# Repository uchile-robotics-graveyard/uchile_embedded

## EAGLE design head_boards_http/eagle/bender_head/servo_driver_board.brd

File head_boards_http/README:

Descripción de la carpeta:
============================

datasheets/: datasheets útiles para el proyecto. Notar que no están realmente en ésta
             carpeta, sino que sólo se hace referencia a ellos. Realmente están en el
             Dropbox de Bender. (carpeta "./New Face")

design/  : datos sobre el diseño de las placas

eagle/   : contiene proyecto para eagle con las placas del nuevas de la cabeza 
           (excepto la de los leds --> CONSEGUIRLA Y AGREGARLA AL GIT!!)

MPLABXProjects/: contiene proyecto mplab con el código para la placa principal y
           y la placa de los servos.

           Además, contiene código de ejemplo para la comunicación i2c y el uso de pwm

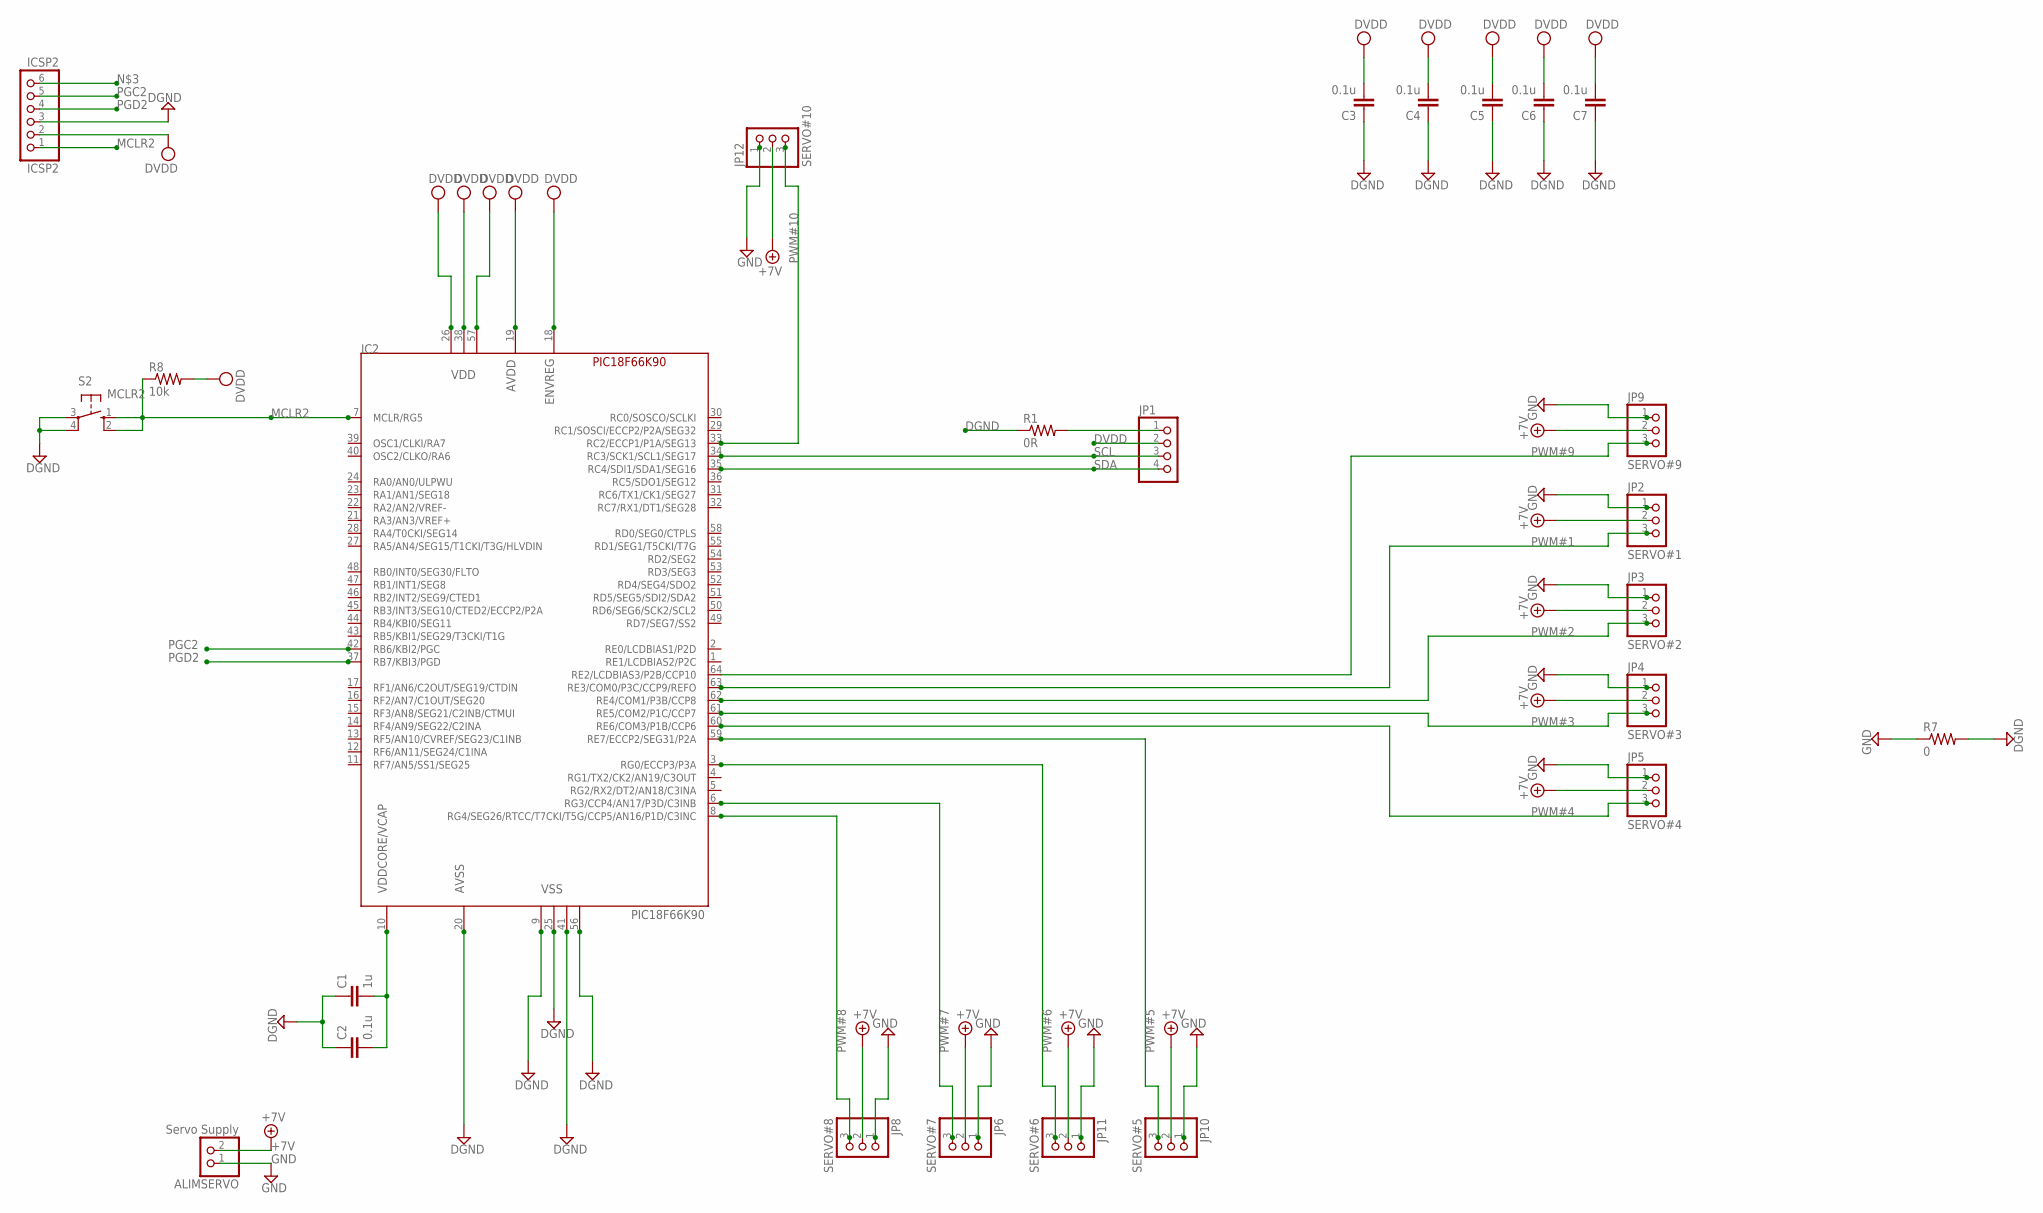
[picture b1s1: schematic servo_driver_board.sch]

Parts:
ALIMSERVO: Servo Supply; 1X02
C1: 1u; C0805
C2, C3, C4, C5, C6, C7: 0.1u; C0805
IC2: PIC18F66K90; TQFP64-10X10
ICSP2: ICSP2; 1X06
JP1: PINHD-1X4/90; 1X04/90
JP2: SERVO#1; 1X03
JP3: SERVO#2; 1X03
JP4: SERVO#3; 1X03
JP5: SERVO#4; 1X03
JP6: SERVO#7; 1X03
JP8: SERVO#8; 1X03
JP9: SERVO#9; 1X03
JP10: SERVO#5; 1X03
JP11: SERVO#6; 1X03
JP12: SERVO#10; 1X03
R1: 0R; R1206
R7: 0; R1206
R8: 10k; R1206
S2: MCLR2; B3F-10XX

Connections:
+7V: ALIMSERVO.2, JP2.2, JP3.2, JP4.2, JP5.2, JP6.2, JP8.2, JP9.2, JP10.2, JP11.2, JP12.2
DGND: C1.1, C2.1, C3.1, C4.1, C5.1, C6.1, C7.1, IC2.9 (VSS), IC2.20 (AVSS), IC2.25 (VSS), IC2.41 (VSS), IC2.56 (VSS), ICSP2.3, R1.1, R7.2, S2.3, S2.4 (P1)
DVDD: C3.2, C4.2, C5.2, C6.2, C7.2, IC2.18 (ENVREG), IC2.19 (AVDD), IC2.26 (VDD), IC2.38 (VDD), IC2.57 (VDD), ICSP2.2, JP1.2, R8.2
GND: ALIMSERVO.1, JP2.1, JP3.1, JP4.1, JP5.1, JP6.1, JP8.1, JP9.1, JP10.1, JP11.1, JP12.1, R7.1
MCLR2: IC2.7 (MCLR/RG5), ICSP2.1, R8.1, S2.1 (S), S2.2 (S1)
unnamed: JP1.1, R1.2
unnamed: C1.2, C2.2, IC2.10 (VDDCORE/VCAP)
PGC2: IC2.42 (RB6/KBI2/PGC), ICSP2.5
PGD2: IC2.37 (RB7/KBI3/PGD), ICSP2.4
PWM#1: IC2.63 (RE3/COM0/P3C/CCP9/REFO), JP2.3
PWM#2: IC2.62 (RE4/COM1/P3B/CCP8), JP3.3
PWM#3: IC2.61 (RE5/COM2/P1C/CCP7), JP4.3
PWM#4: IC2.60 (RE6/COM3/P1B/CCP6), JP5.3
PWM#5: IC2.59 (RE7/ECCP2/SEG31/P2A), JP10.3
PWM#6: IC2.3 (RG0/ECCP3/P3A), JP11.3
PWM#7: IC2.6 (RG3/CCP4/AN17/P3D/C3INB), JP6.3
PWM#8: IC2.8 (RG4/SEG26/RTCC/T7CKI/T5G/CCP5/AN16/P1D/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), JP8.3
PWM#9: IC2.64 (RE2/LCDBIAS3/P2B/CCP10), JP9.3
PWM#10: IC2.33 (RC2/ECCP1/P1A/SEG13), JP12.3
SCL: IC2.34 (RC3/SCK1/SCL1/SEG17), JP1.3
SDA: IC2.35 (RC4/SDI1/SDA1/SEG16), JP1.4

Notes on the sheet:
PWM#1
PWM#2
PWM#3
PWM#4
PWM#7
PWM#8
PWM#9
PWM#5
PWM#6
PWM#10

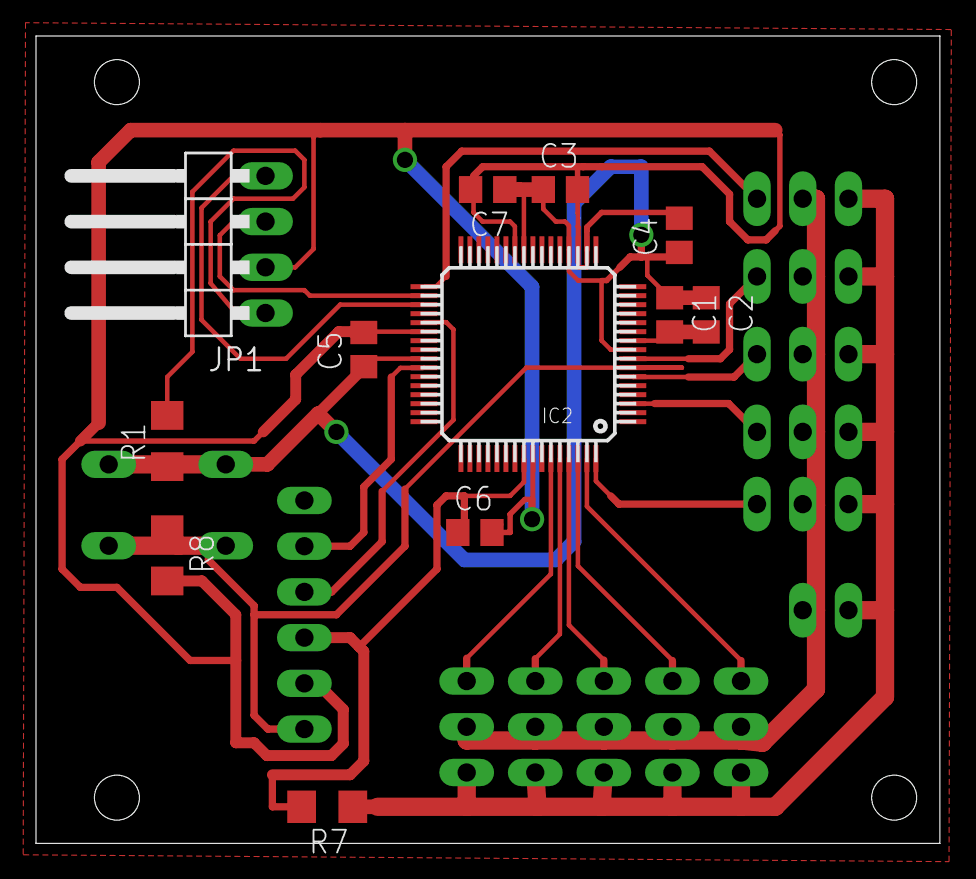
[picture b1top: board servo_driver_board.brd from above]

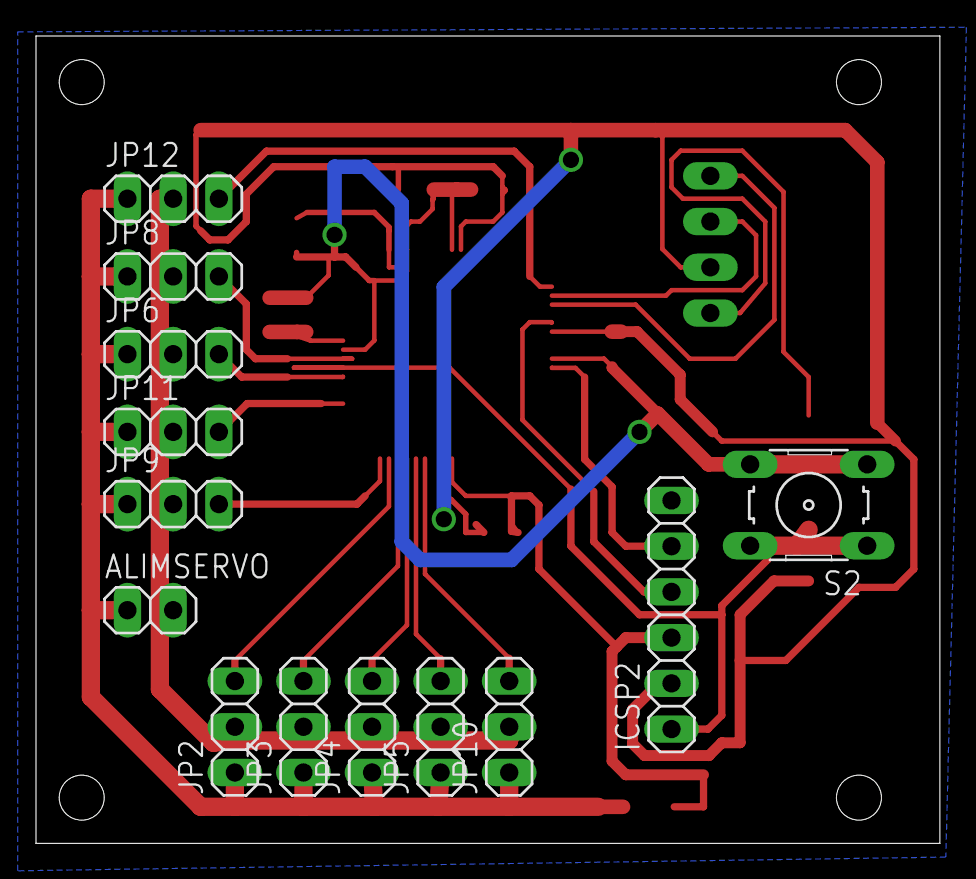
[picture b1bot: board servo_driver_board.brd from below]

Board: 2 copper layers, 50.2 x 44.9 mm, 25 parts (13 on the bottom side), 21 nets.

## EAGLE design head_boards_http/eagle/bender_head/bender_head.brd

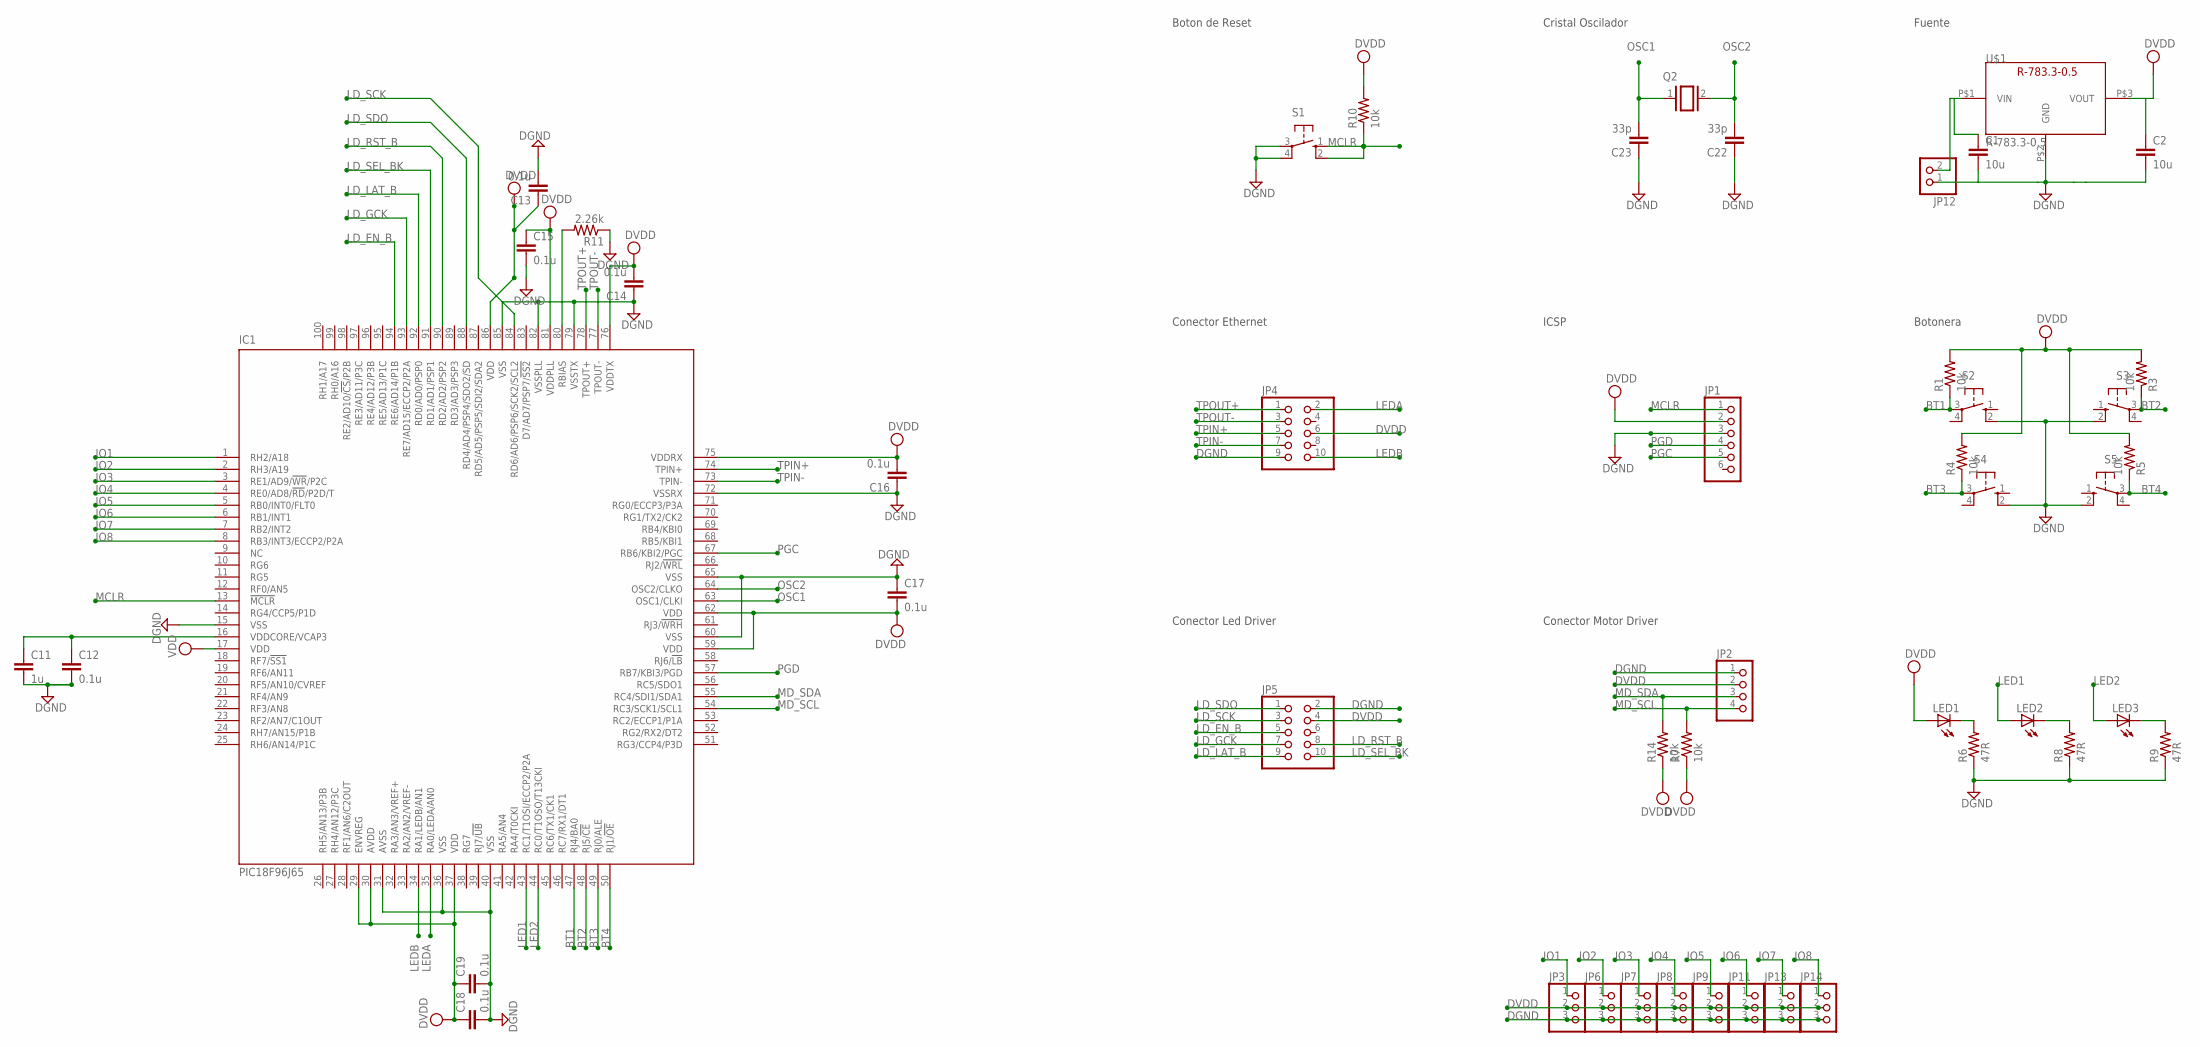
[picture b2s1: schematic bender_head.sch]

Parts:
C1, C2: 10u; C1206
C11: 1u; C1206
C12, C13, C14, C15, C16, C17, C18, C19: 0.1u; C0805
C22, C23: 33p; C1206
IC1: PIC18F96J65; TQFP100
JP1: PINHD-1X6; 1X06
JP2: PINHD-1X4/90; 1X04/90
JP3, JP6, JP7, JP8, JP9, JP11, JP13, JP14: PINHD-1X3; 1X03
JP4, JP5: PINHD-2X5/90; 2X05/90
JP12: PINHD-1X2/90; 1X02/90
LED1, LED2, LED3: LEDSML0805; SML0805
Q2: XTAL/S; QS
R1, R3, R4, R5, R7, R10, R14: 10k; R1206
R6: 47R; M0805
R8, R9: 47R; M1206
R11: 2.26k; R1206
S1, S2, S3, S4, S5: 10-XX; B3F-10XX
U$1: R-783.3-0.5

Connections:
BT1: IC1.47 (RJ4/BA0), R1.1, S2.3
BT2: IC1.48 (RJ5/!CE), R3.1, S3.3
BT3: IC1.49 (RJ0/ALE), R4.1, S4.3
BT4: IC1.50 (RJ1/!OE), R5.1, S5.3
DGND: C1.2, C2.2, C11.2, C12.2, C13.2, C14.1, C15.2, C16.1, C17.1, C18.2, C19.2, C22.1, C23.1, IC1.15 (VSS), IC1.31 (AVSS), IC1.36 (VSS), IC1.40 (VSS), IC1.60 (VSS), IC1.65 (VSS), IC1.72 (VSSRX), IC1.79 (VSSTX), IC1.82 (VSSPLL), IC1.85 (VSS), JP1.3, JP2.1, JP3.3, JP4.9, JP5.2, JP6.3, JP7.3, JP8.3, JP9.3, JP11.3, JP12.1, JP13.3, JP14.3, R6.1, R8.1, R9.1, R11.1, S1.3, S1.4 (P1), S2.2 (S1), S3.2 (S1), S4.2 (S1), S5.2 (S1), U$1.P$2 (GND)
DVDD: C2.1, C13.1, C14.2, C15.1, C16.2, C17.2, C18.1, C19.1, IC1.17 (VDD), IC1.29 (ENVREG), IC1.30 (AVDD), IC1.37 (VDD), IC1.59 (VDD), IC1.62 (VDD), IC1.75 (VDDRX), IC1.76 (VDDTX), IC1.81 (VDDPLL), IC1.86 (VDD), JP1.2, JP2.2, JP3.2, JP4.6, JP5.4, JP6.2, JP7.2, JP8.2, JP9.2, JP11.2, JP13.2, JP14.2, LED1.A, R1.2, R3.2, R4.2, R5.2, R7.1, R10.2, R14.1, U$1.P$3 (VOUT)
IO1: IC1.1 (RH2/A18), JP3.1
IO2: IC1.2 (RH3/A19), JP6.1
IO3: IC1.3 (RE1/AD9/!WR!/P2C), JP7.1
IO4: IC1.4 (RE0/AD8/!RD!/P2D/T), JP8.1
IO5: IC1.5 (RB0/INT0/FLT0), JP9.1
IO6: IC1.6 (RB1/INT1), JP11.1
IO7: IC1.7 (RB2/INT2), JP13.1
IO8: IC1.8 (RB3/INT3/ECCP2/P2A), JP14.1
LD_EN_B: IC1.94 (RE6/AD14/P1B), JP5.5
LD_GCK: IC1.93 (RE7/AD15/ECCP2/P2A), JP5.7
LD_LAT_B: IC1.92 (RD0/AD0/PSP0), JP5.9
LD_RST_B: IC1.90 (RD2/AD2/PSP2), JP5.8
LD_SCK: IC1.84 (RD6/AD6/PSP6/SCK2/SCL2), JP5.3
LD_SDO: IC1.88 (RD4/AD4/PSP4/SDO2/SD), JP5.1
LD_SEL_BK: IC1.91 (RD1/AD1/PSP1), JP5.10
LED1: IC1.43 (RC1/T1OSI/ECCP2/P2A), LED2.A
LED2: IC1.44 (RC0/T1OSO/T13CKI), LED3.A
LEDA: IC1.35 (RA0/LEDA/AN0), JP4.2
LEDB: IC1.34 (RA1/LEDB/AN1), JP4.10
MCLR: IC1.13 (!MCLR), JP1.1, R10.1, S1.1 (S), S1.2 (S1)
MD_SCL: IC1.54 (RC3/SCK1/SCL1), JP2.4, R7.2
MD_SDA: IC1.55 (RC4/SDI1/SDA1), JP2.3, R14.2
unnamed: LED1.C, R6.2
unnamed: LED2.C, R8.2
unnamed: LED3.C, R9.2
unnamed: C11.1, C12.1, IC1.16 (VDDCORE/VCAP3)
unnamed: IC1.80 (RBIAS), R11.2
OSC1: C23.2, IC1.63 (OSC1/CLKI), Q2.1
OSC2: C22.2, IC1.64 (OSC2/CLKO), Q2.2
PGC: IC1.67 (RB6/KBI2/PGC), JP1.5
PGD: IC1.57 (RB7/KBI3/PGD), JP1.4
TPIN+: IC1.74 (TPIN+), JP4.5
TPIN-: IC1.73 (TPIN-), JP4.7
TPOUT+: IC1.78 (TPOUT+), JP4.1
TPOUT-: IC1.77 (TPOUT-), JP4.3
VIN: C1.1, JP12.2, U$1.P$1 (VIN)

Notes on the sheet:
Conector Ethernet
Cristal Oscilador
Boton de Reset
Conector Led Driver
Conector Motor Driver
ICSP
Botonera
Fuente

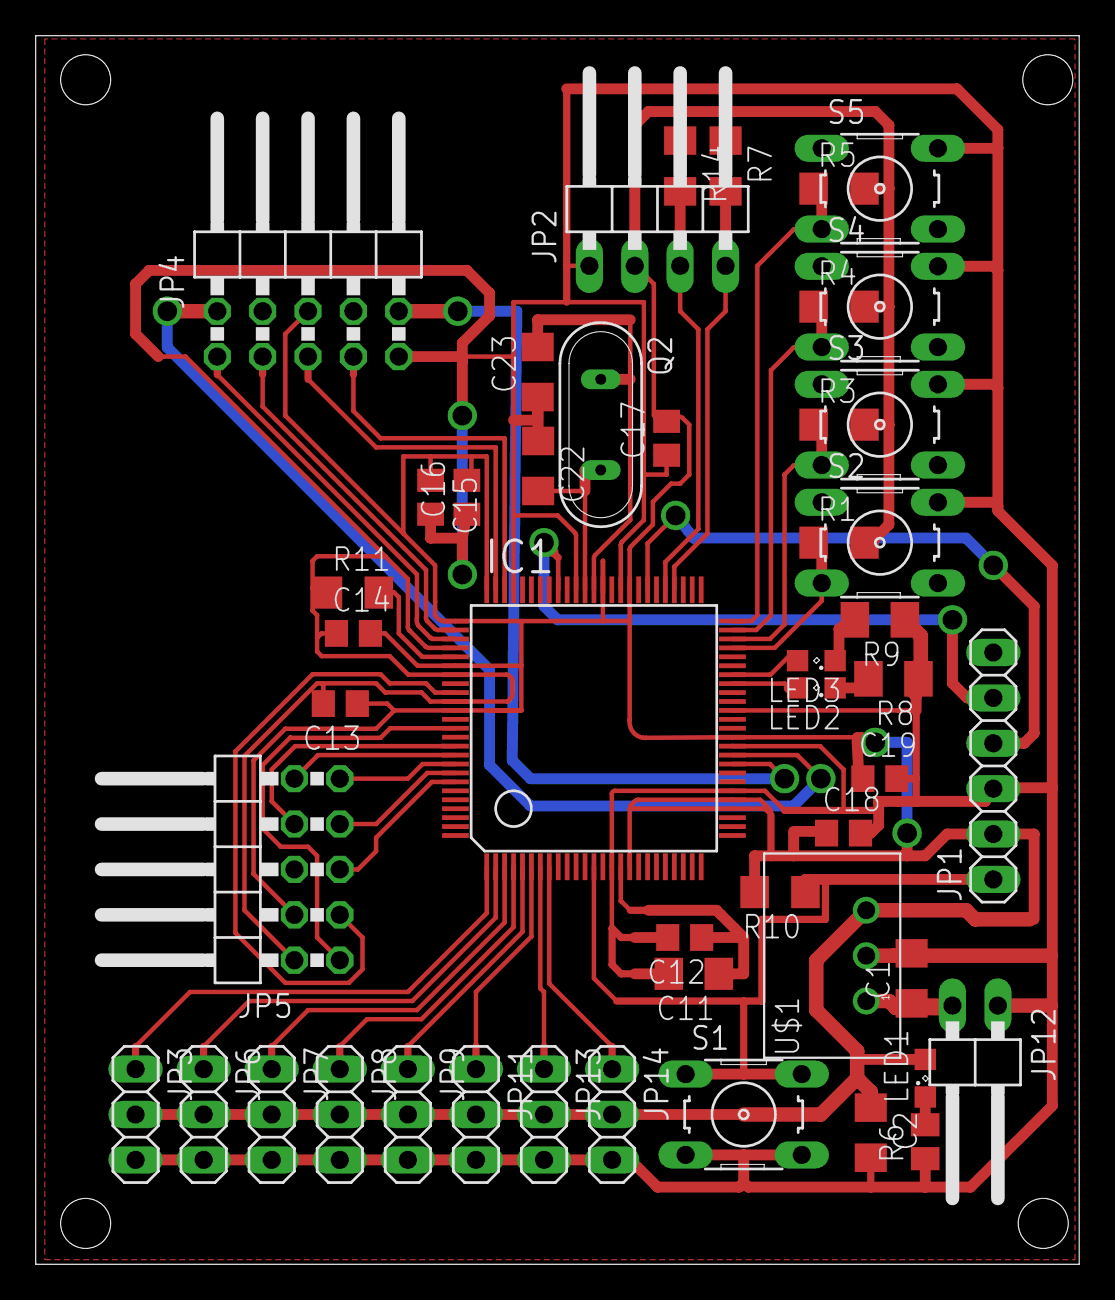
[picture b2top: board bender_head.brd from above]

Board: 2 copper layers, 58.4 x 68.8 mm, 48 parts (0 on the bottom side), 42 nets.

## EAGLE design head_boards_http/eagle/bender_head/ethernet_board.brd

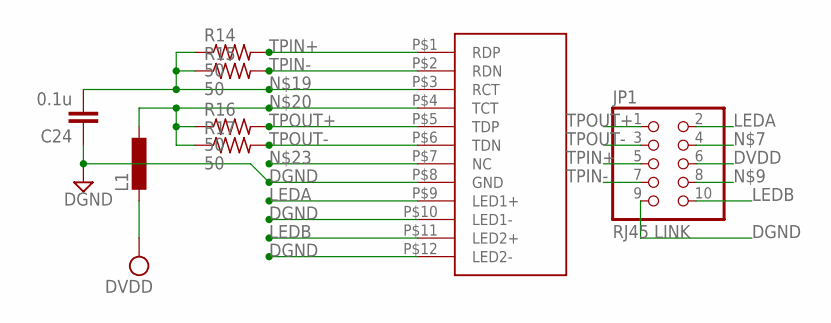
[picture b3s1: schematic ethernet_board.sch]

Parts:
C24: 0.1u; C0805
JP1: RJ45 LINK; 2X05/90
L1: L-EU0207/10; 0207/10
R14, R15, R16, R17: 50; R1206
U$5: RJ45; TYCO-RJ45

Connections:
DGND: C24.1, JP1.9, U$5.P$8 (GND), U$5.P$10 (LED1-), U$5.P$12 (LED2-)
DVDD: JP1.6, L1.2
LEDA: JP1.2, U$5.P$9 (LED1+)
LEDB: JP1.10, U$5.P$11 (LED2+)
unnamed: C24.2, R14.1, R15.1, U$5.P$3 (RCT)
unnamed: L1.1, R16.1, R17.1, U$5.P$4 (TCT)
TPIN+: JP1.5, R14.2, U$5.P$1 (RDP)
TPIN-: JP1.7, R15.2, U$5.P$2 (RDN)
TPOUT+: JP1.1, R16.2, U$5.P$5 (TDP)
TPOUT-: JP1.3, R17.2, U$5.P$6 (TDN)

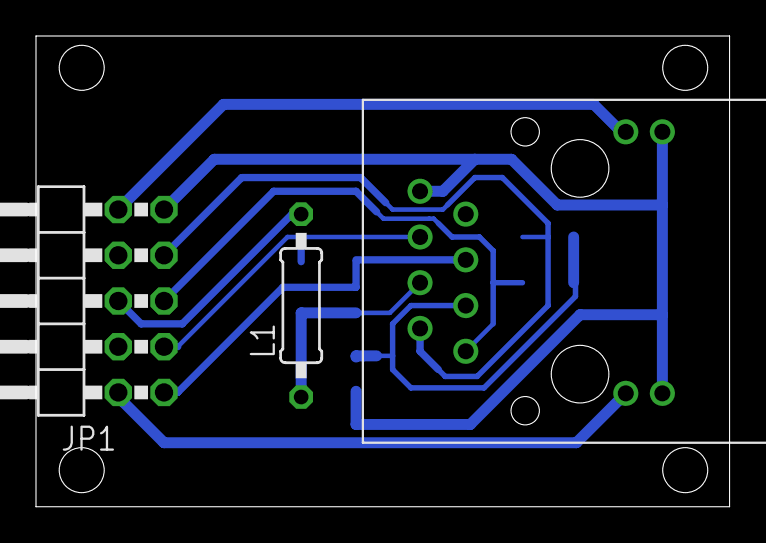
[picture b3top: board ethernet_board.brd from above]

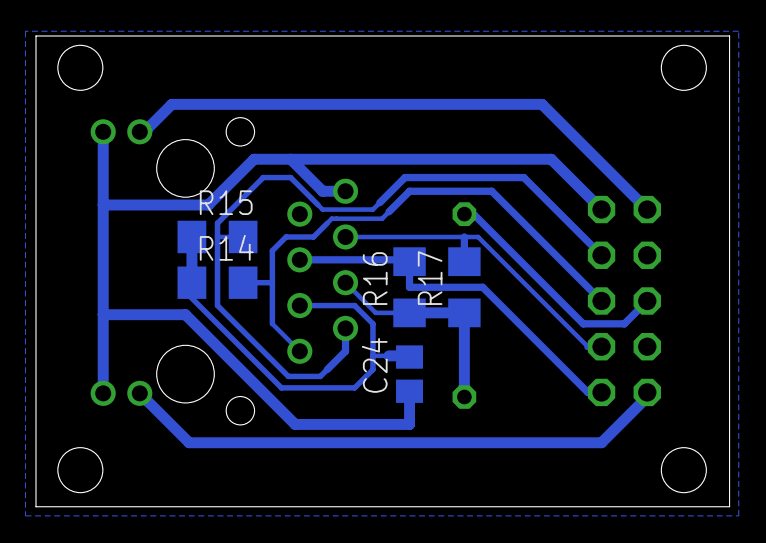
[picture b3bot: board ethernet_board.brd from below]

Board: 2 copper layers, 38.5 x 26.2 mm, 8 parts (5 on the bottom side), 10 nets.

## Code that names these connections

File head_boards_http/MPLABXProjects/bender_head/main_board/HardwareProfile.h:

 /*********************************************************************
 *
 *	Hardware specific definitions for:
 *    - PIC18F96J60
 *
 *********************************************************************
 * FileName:        HardwareProfile.h
 * Dependencies:    Compiler.h
 * Processor:       PIC18
 * Compiler:        Microchip C18 v3.36 or higher
 * Company:         Microchip Technology, Inc.
 ********************************************************************/
#ifndef HARDWARE_PROFILE_H
#define HARDWARE_PROFILE_H

#include "Compiler.h"

// Set configuration fuses (but only in MainDemo.c where THIS_IS_STACK_APPLICATION is defined)
#if defined(THIS_IS_STACK_APPLICATION)
        // WDT (ON): Watch Dog Timer
	#pragma config WDT=OFF

        /* FOSC2 ( ON ): Default/Reset System Clock Select bit. 
         * - OFF: clock=INTRC,
         * - ON : clock selected by FOSC1:FOSC0
         */
        #pragma config FOSC2=ON

        // FOSC (ECPLL): Oscillator Selection. (HS|EC) osc., (HSPLL|ECPLL) HS|EC-CLKO with PLL..
        #pragma config FOSC=HSPLL


        /* ETHLED( ON ): Ethernet LED Enable bit.
         * - ON : RA0/RA1 are multiplexed with LEDA/LEDB when Ethernet module is
         *        enabled and function as I/O when Ethernet is disabled.
         * - OFF: RA0/RA1 function as I/O regardless of Ethernet module status.
         */
        #pragma config ETHLED=ON

        /* CCP2MX( ON ): ECCP2 MUX bit.
         *  - ON :ECCP2/P2A is multiplexed with RC1.
         *  - OFF:ECCP2/P2A is multiplexed with:
         *         - RE7 in Microcontroller mode
         *         - RB3 in Extended Microcontroller mode
         */
        #pragma config CCP2MX=OFF
        
        /*ECCPMX( ON ): ECCP MUX bit. ECCP1(P1B/P1C) and ECCP3(P3B/P3C) outputs are multiplexed with:
         * - ON : RE6/RE5 and RE4/RE3
         * - OFF: RH7/RH6 and RH5/RH4
         */
        #pragma config ECCPMX=OFF

        /* Other configs:
         * STVR  ( ON ): Stack Overflow/Underflow Reset
         * DEBUG (OFF ): Background Debbuger - RB6,RB7 for In-Circuit Debug
         * CP0   (OFF ): Code Protection bit
         * FCMEN ( ON ): Fail-Safe Clock Monitor
         * IESO  ( ON ): Two-Speed Start-up (Internal/External Oscillator Switchover) Control
         * WDTPS(32768): Watchdog Timer Postscaler Select bits. Values: 0x0N --> 1:N
         * EASHFT( ON ): External Address Bus Shift Enable
         * MODE  ( MM ): External Memory Bus 
         *               (XM20|XM16|XM12): Extended microcontroller mode, N-Bit Address mode.
         *               (MM) Microcontroller mode. Ex. uC disabled
         * BW    ( 16 ): Data Bus Width Select bit (8|16)
         * WAIT  (OFF ): External Bus Wait Enable bit
         */

	// Automatically set Extended Instruction Set fuse based on compiler setting
        // XINST ( ON ): Extended Instruction Set
	#if defined(__EXTENDED18__)
		#pragma config XINST=ON
	#else
		#pragma config XINST=OFF
	#endif
#endif


// Clock frequency values
// These directly influence timed events using the Tick module.  They also are used for UART and SPI baud rate generation.
#define GetSystemClock()		(41666667ul)			// Hz
#define GetInstructionClock()	(GetSystemClock()/4)	// Normally GetSystemClock()/4 for PIC18, GetSystemClock()/2 for PIC24/dsPIC, and GetSystemClock()/1 for PIC32.  Might need changing if using Doze modes.
#define GetPeripheralClock()	(GetSystemClock()/4)	// Normally GetSystemClock()/4 for PIC18, GetSystemClock()/2 for PIC24/dsPIC, and GetSystemClock()/1 for PIC32.  Divisor may be different if using a PIC32 since it's configurable.


// Hardware I/O pin mappings

// LED DRIVER
#define LD_RST_B_TRIS	(TRISDbits.TRISD2)
#define LD_RST_B	(PORTDbits.RD2)
#define LD_SEL_BK_TRIS	(TRISDbits.TRISD1)
#define LD_SEL_BK	(PORTDbits.RD1)
#define LD_LAT_B_TRIS	(TRISDbits.TRISD0)
#define LD_LAT_B	(PORTDbits.RD0)
#define LD_GCK_TRIS	(TRISEbits.TRISE7)
#define LD_GCK		(PORTEbits.RE7)
#define LD_EN_B_TRIS	(TRISEbits.TRISE6)
#define LD_EN_B		(PORTEbits.RE6)

// Momentary push buttons
#define BUTTON0_TRIS	(TRISJbits.TRISJ4) // Ref S5
#define	BUTTON0_IO	(PORTJbits.RJ4)
#define BUTTON1_TRIS	(TRISJbits.TRISJ5) // Ref S4
#define	BUTTON1_IO	(PORTJbits.RJ5)
#define BUTTON2_TRIS	(TRISJbits.TRISJ0) // Ref S3
#define	BUTTON2_IO	(PORTJbits.RJ0)
#define BUTTON3_TRIS	(TRISJbits.TRISJ1) // Ref S2
#define	BUTTON3_IO	(PORTJbits.RJ1)

// Ethernet TPIN+/- polarity swap circuitry (PICDEM.net 2 Rev 6)
#define ETH_RX_POLARITY_SWAP_TRIS (TRISGbits.TRISG0)
#define ETH_RX_POLARITY_SWAP_IO   (LATGbits.LATG0)

// UART mapping functions for consistent API names across 8-bit and 16 or
// 32 bit compilers.  For simplicity, everything will use "UART" instead
// of USART/EUSART/etc.
#define BusyUART()        BusyUSART()
#define CloseUART()       CloseUSART()
#define ConfigIntUART(a)  ConfigIntUSART(a)
#define DataRdyUART()     DataRdyUSART()
#define OpenUART(a,b,c)   OpenUSART(a,b,c)
#define ReadUART()        ReadUSART()
#define WriteUART(a)      WriteUSART(a)
#define getsUART(a,b,c)   getsUSART(b,a)
#define putsUART(a)       putsUSART(a)
//#define getcUART()        ReadUSART()
//#define putcUART(a)       WriteUSART(a)
#define putrsUART(a)      putrsUSART((far rom char*)a)

#endif // #ifndef HARDWARE_PROFILE_H

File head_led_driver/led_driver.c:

//#fuses INTRC_IO,NOMCLR,NOWDT,NOPROTECT,NOLVP,PUT,BROWNOUT // Opciones de configuración
#pragma config WDTE = OFF       // NOWDT
#pragma config CPD = OFF        // NOPROTECT   data memory code protection off
#pragma config MCLRE = OFF      // NOMCLR
#pragma config LVP = OFF        // NOLVP
#pragma config FOSC = (4000000L)  // INTRC_IO   oscilador
#pragma config BOREN = ON       // BROWNOUT
#pragma config PWRTE = ON       // PUT

#include <xc.h>
#include <conio.h>
#include <pic16f628a.h>
#include "uart.h"

#define  Led0   RB0    // PIN_B0
#define  Led1   RB3    // PIN_B3
#define  Led2   RB4    // PIN_B4
#define  Led3   RB5    // PIN_B5
#define  Led4   RB6    // PIN_B6
#define  Led5   RB7    // PIN_B7

// Interfaces para compatibilizar con el compilador antiguo
#define output_high(_X) _X=1
#define output_low(_X) _X=0
#define delay(_X) __delay(_X)
#define delay_ms(_X) __delay_ms(_X)
#define delay_us(_X) __delay_us(_X)


// Variables globales
char comando[3];
char indiceComando=0;
char aux;
unsigned char refbrillo[6];
unsigned char brillo[6];
unsigned char vel[6];
unsigned char espera[6];

/*
    comandos:   255   10n   x  elige el brillo a x porcentaje ( 0 - 254 )del led n
                255   11n   x  elige la velocidad con la que cambia el brillo
                255   120   x  apaga todos los leds
*/

void analizaComando(){
   switch(comando[1])
   {
      case 100:
            refbrillo[0]=comando[2];
            break;
      case  101:
            refbrillo[1]=comando[2];
            break;
      case  102:
            refbrillo[2]=comando[2];
            break;
      case  103:
            refbrillo[3]=comando[2];
            break;
      case  104:
            refbrillo[3]=comando[2];
            break;
      case  105:
            refbrillo[5]=comando[2];
            break;

      case  110:
            vel[0]=comando[2];
            break;
      case  111:
            vel[1]=comando[2];
            break;
      case  112:
            vel[2]=comando[2];
            break;
      case  113:
            vel[3]=comando[2];
            break;
      case  114:
            vel[4]=comando[2];
            break;
      case  115:
            vel[5]=comando[2];
            break;

      case  120:
            vel[0]=0;
            vel[1]=0;
            vel[2]=0;
            vel[3]=0;
            vel[4]=0;
            vel[5]=0;
            refbrillo[0]=0;
            refbrillo[1]=0;
            refbrillo[2]=0;
            refbrillo[3]=0;
            refbrillo[4]=0;
            refbrillo[5]=0;
            brillo[0]=0;
            brillo[1]=0;
            brillo[2]=0;
            brillo[3]=0;
            brillo[4]=0;
            brillo[5]=0;
            break;

      default:
            break;


   }

   return;
}



void serial_isr()
{
   if(UART_Data_Ready())
   {
      aux=UART_Read();
      if(aux==255)
      {
         comando[0]=aux;
         indiceComando=1;
         return;
      }
      else if(indiceComando==1)
      {
         comando[1]=aux;
         indiceComando=2;
         return;
      }
      else if(indiceComando==2)
      {
         comando[2]=aux;
         indiceComando=3;
         analizaComando();
         return;
      }
   }
  return;
 }
 
  


void apagatodo()
{
   output_low(Led0);
   output_low(Led1);
   output_low(Led2);
   output_low(Led3);
   output_low(Led4);
   output_low(Led5);
}

void encendertodo()
{

   output_high(Led0);
   output_high(Led1);
   output_high(Led2);
   output_high(Led3);
   output_high(Led4);
   output_high(Led5);

}

void  main()
{
   int   i=0;
   for(i=0;i<5;++i)
   {
      vel[i]=0;
      brillo[i]=0;
      refbrillo[i]=0;
      espera[i]=0;
   }
   delay_ms(1000);
   apagatodo();
   output_high(Led0);
   delay_ms(1000);
   apagatodo();
   output_high(Led1);
   delay_ms(1000);
   apagatodo();
   output_high(Led2);
   delay_ms(1000);
   apagatodo();
   output_high(Led3);
   delay_ms(1000);
   apagatodo();
   output_high(Led4);
   delay_ms(1000);
   apagatodo();
   output_high(Led5);
   delay_ms(1000);
   apagatodo();
   delay_ms(2000);
   ei();

   // Enable interrupts
   INTCONbits.GIE = 1;
   UART_Init(BAUDRATE);


   while(1)
   {
      serial_isr();
      if(brillo[0]!=0)
         output_high(Led0);
      if(brillo[1]!=0)
         output_high(Led2);
      if(brillo[2]!=0)
         output_high(Led2);
      if(brillo[3]!=0)
         output_high(Led3);
      if(brillo[4]!=0)
         output_high(Led4);
      if(brillo[5]!=0)
         output_high(Led5);

      for(i=0;i<255;++i)
      {
         if(brillo[0]==i)
            output_low(Led0);
         if(brillo[1]==i)
            output_low(Led1);
         if(brillo[2]==i)
            output_low(Led2);
         if(brillo[3]==i)
            output_low(Led3);
         if(brillo[4]==i)
            output_low(Led4);
         if(brillo[5]==i)
            output_low(Led5);
         delay_us(1);
      }
      for(i=0;i<6;++i)
      {
         if(espera[i]!=0)
            espera[i]--;
         if(brillo[i]!=refbrillo[i])
         {
            if(espera[i]==0)
            {
               espera[i]=vel[i];
               if(brillo[i]>refbrillo[i])
               {
                  --brillo[i];
               }
               else
               {
                  ++brillo[i];
               }
            }
         }
      }
   }
}

int test()
{
  INTCONbits.GIE = 1;
  TRISB = 0xFF; //PORTB as Input
  UART_Init(9600);
  TRISB4=0;  //puerto B4 como salida
  TRISB5=0;   // puerto B5 como salida


  do {
        while(!RCIF)
        {
            RB5 = 1;
        }
        RB5 = 0;
        char data = RCREG;
        if(data==0x01) RB4 = 1;
        else RB4 = 0;
  }
  while(1);
}

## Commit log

2016-01-29 head controller
2016-02-21 Código de placas para cabeza nueva, basadas en comunicación HTTP
2016-04-13 Primera prueba rs485
2016-07-05 Version ROS fuerte de bender_head_Arduino
2016-07-25 Elimino versiones antiguas y renombro actuales
2016-07-26 Agrego capas de Abstracción
2016-07-29 Version estable del Package. Probada en Bender
2016-07-30 README.md edited online with Bitbucket
2016-07-31 Agrego lista de colores
2016-08-26 Actualizo tareas pendientes y agrego cmd para joystick
2016-09-18 Fix issues with new version of Dynamixel library
